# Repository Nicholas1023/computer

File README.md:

# Nicholas's 1-Bit Logic Gate Computer
Hello I am Nicholas (@Nicholas1023 on the Hack Club Slack), and this is my first PCB, which A 1-bit computer that uses NOR and NOT gates as its processor, Push buttons as input, and LEDs as output.
## 3D View
<br>**Board size: 53.55x49.05 mm**<br>**Note:** The processor symbol next to the transistors is not a component.
## PCB Layout

## Schematic

## Bill of Materials
|Qty|Ref. Designator |Name                 |Mounting Type|
|:-:|:---------------|:--------------------|:------------|
|1  |BT1             |CR2032 Battery holder|SMD          |
|1  |R1              |Resistor             |THT          |
|1  |J1              |1x04 2.54mm Connector|THT          |
|3  |D1, D2, D3 (LED)|5mm LED              |THT          |
|3  |SW1, SW2, SW3   |6mm Push button      |THT          |
|3  |Q1, Q2, Q3      |2N3904 NPN Transistor|THT          |
## Pinout
GND: Ground<br>+3V: +3V Power<br>NOR: NOR Output<br>NOT: NOT Output

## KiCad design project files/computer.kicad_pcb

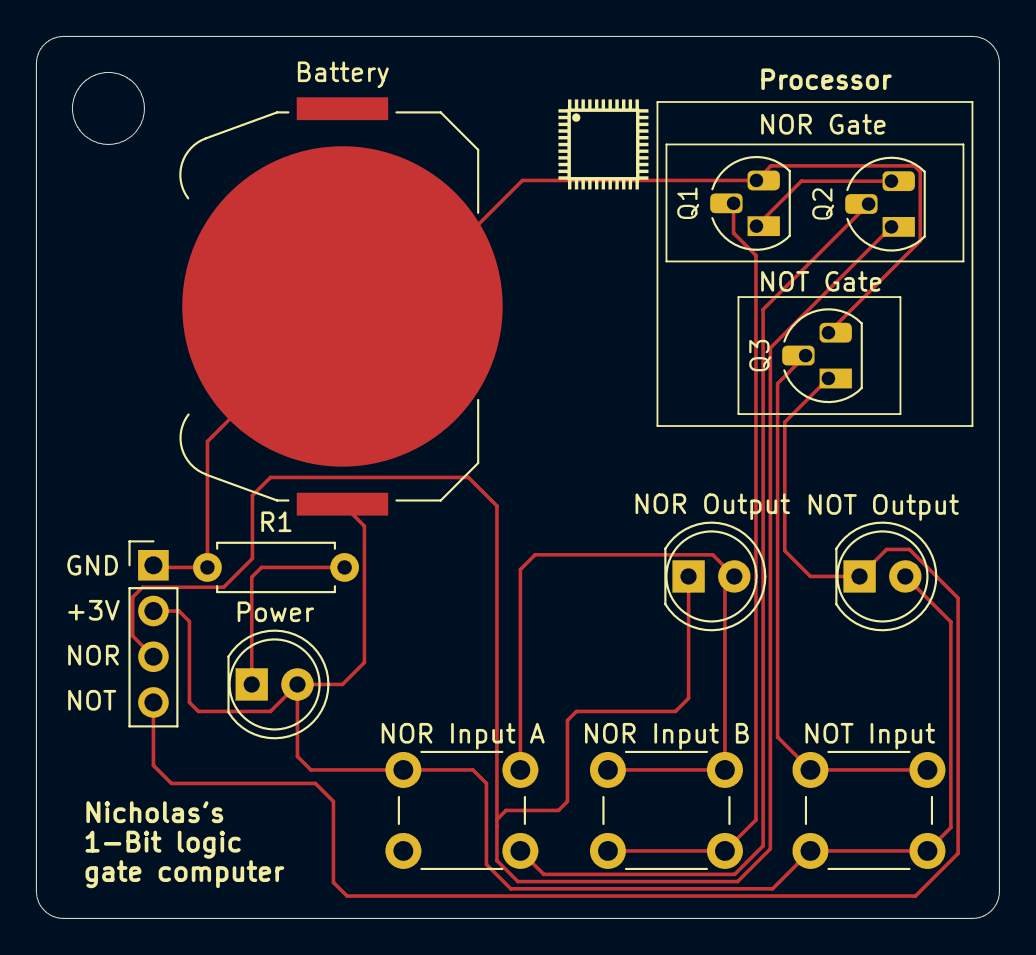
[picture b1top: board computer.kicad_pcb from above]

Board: 2 copper layers, 53.5 x 49.0 mm, 12 parts (0 on the bottom side), 9 nets.

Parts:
Battery: Battery_Cell; BatteryHolder_Keystone_3034_1x20mm
J1: Conn_01x04_Pin; PinHeader_1x04_P2.54mm_Vertical
NOR Input A: NOR Input (A); SW_PUSH_6mm
NOR Input B: NOR Input (B); SW_PUSH_6mm
NOR Output: NOR Output; LED_D5.0mm
NOT Input: NOT Input; SW_PUSH_6mm
NOT Output: NOT Output; LED_D5.0mm
Power: Power; LED_D5.0mm
Q1, Q2, Q3: NPN; TO-92L_HandSolder
R1: R; R_Axial_DIN0207_L6.3mm_D2.5mm_P7.62mm_Horizontal

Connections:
unnamed: Battery.1 (+), J1.2, NOR Input A.1, NOR Input B.1, NOR Output.2 (A), NOT Input.2, NOT Output.2 (A), Power.2 (A)
unnamed: Battery.2 (-), J1.1, Q1.3 (E), Q3.3 (E), R1.2
unnamed: J1.4, NOT Output.1 (K), Q3.1 (C)
unnamed: J1.3, NOR Output.1 (K), Q2.1 (C)
unnamed: Power.1 (K), R1.1
unnamed: NOR Input B.2, Q1.2 (B)
unnamed: Q1.1 (C), Q2.3 (E)
unnamed: NOR Input A.2, Q2.2 (B)
unnamed: NOT Input.1, Q3.2 (B)

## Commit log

2025-04-12 Update PCB with rounded corners (Images)
2025-04-12 Update images with rounded PCB corners.
2025-04-13 Upload production file
2025-04-16 Update silkscreen text
2025-04-21 Upload 3D model files
